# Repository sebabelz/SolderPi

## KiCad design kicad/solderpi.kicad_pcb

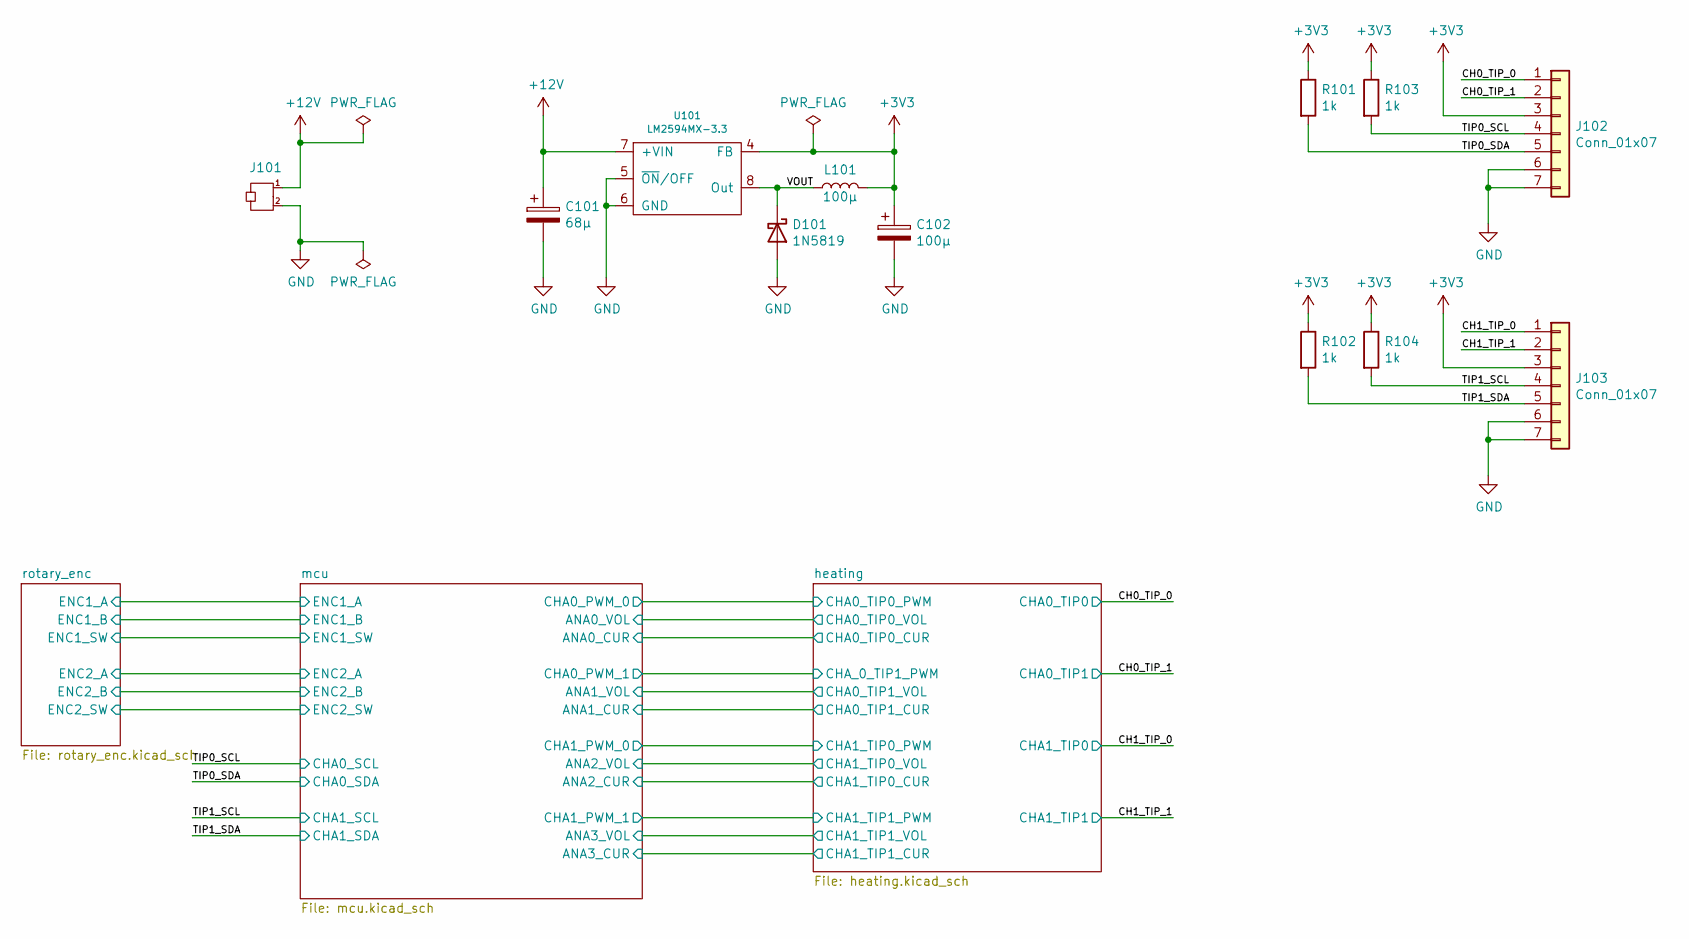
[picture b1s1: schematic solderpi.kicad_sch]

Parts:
C101: 68µ; CP_EIA-7343-30_AVX-N; Digikey 478-11114-1-ND
C102: 100µ; CP_EIA-7343-30_AVX-N; Digikey 478-9140-1-ND
D101: 1N5819; D_SOD-123; Digikey 1N5819HW-FDICT-ND
J101: CON_ULTRAFIT; ULTRAFIT_2_90; Digikey WM11586-ND
J102, J103: Conn_01x07; NANOFIT_7_90; Digikey WM16898-ND
L101: 100µ; L_Bourns_SRR0735A; Digikey SRR0735A-101MCT-ND
R101, R102, R103, R104: 1k; R_0603_1608Metric; Digikey RMCF0603FT1K00CT-ND
U101: LM2594MX-3.3; SOIC-8-1EP_3.9x4.9mm_P1.27mm_EP2.95x4.9mm_Mask2.71x3.4mm; Digikey LM2594MX-3.3/NOPBCT-ND

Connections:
+3V3: C102.1, J102.3, J103.3, L101.2, R101.1, R102.1, R103.1, R104.1, U101.4 (FB); also elsewhere on the board
+12V: C101.1, J101.1, U101.7 (+VIN); also elsewhere on the board
/CH0_TIP_0: J102.1; also elsewhere on the board
/CH0_TIP_1: J102.2; also elsewhere on the board
/CH1_TIP_0: J103.1; also elsewhere on the board
/CH1_TIP_1: J103.2; also elsewhere on the board
/TIP0_SCL: J102.4, R103.2; also elsewhere on the board
/TIP0_SDA: J102.5, R101.2; also elsewhere on the board
/TIP1_SCL: J103.4, R104.2; also elsewhere on the board
/TIP1_SDA: J103.5, R102.2; also elsewhere on the board
/VOUT: D101.1 (K), L101.1, U101.8 (Out)
GND: C101.2, C102.2, D101.2 (A), J101.2, J102.6, J102.7, J103.6, J103.7, U101.5 (~ON/OFF), U101.6 (GND); also elsewhere on the board

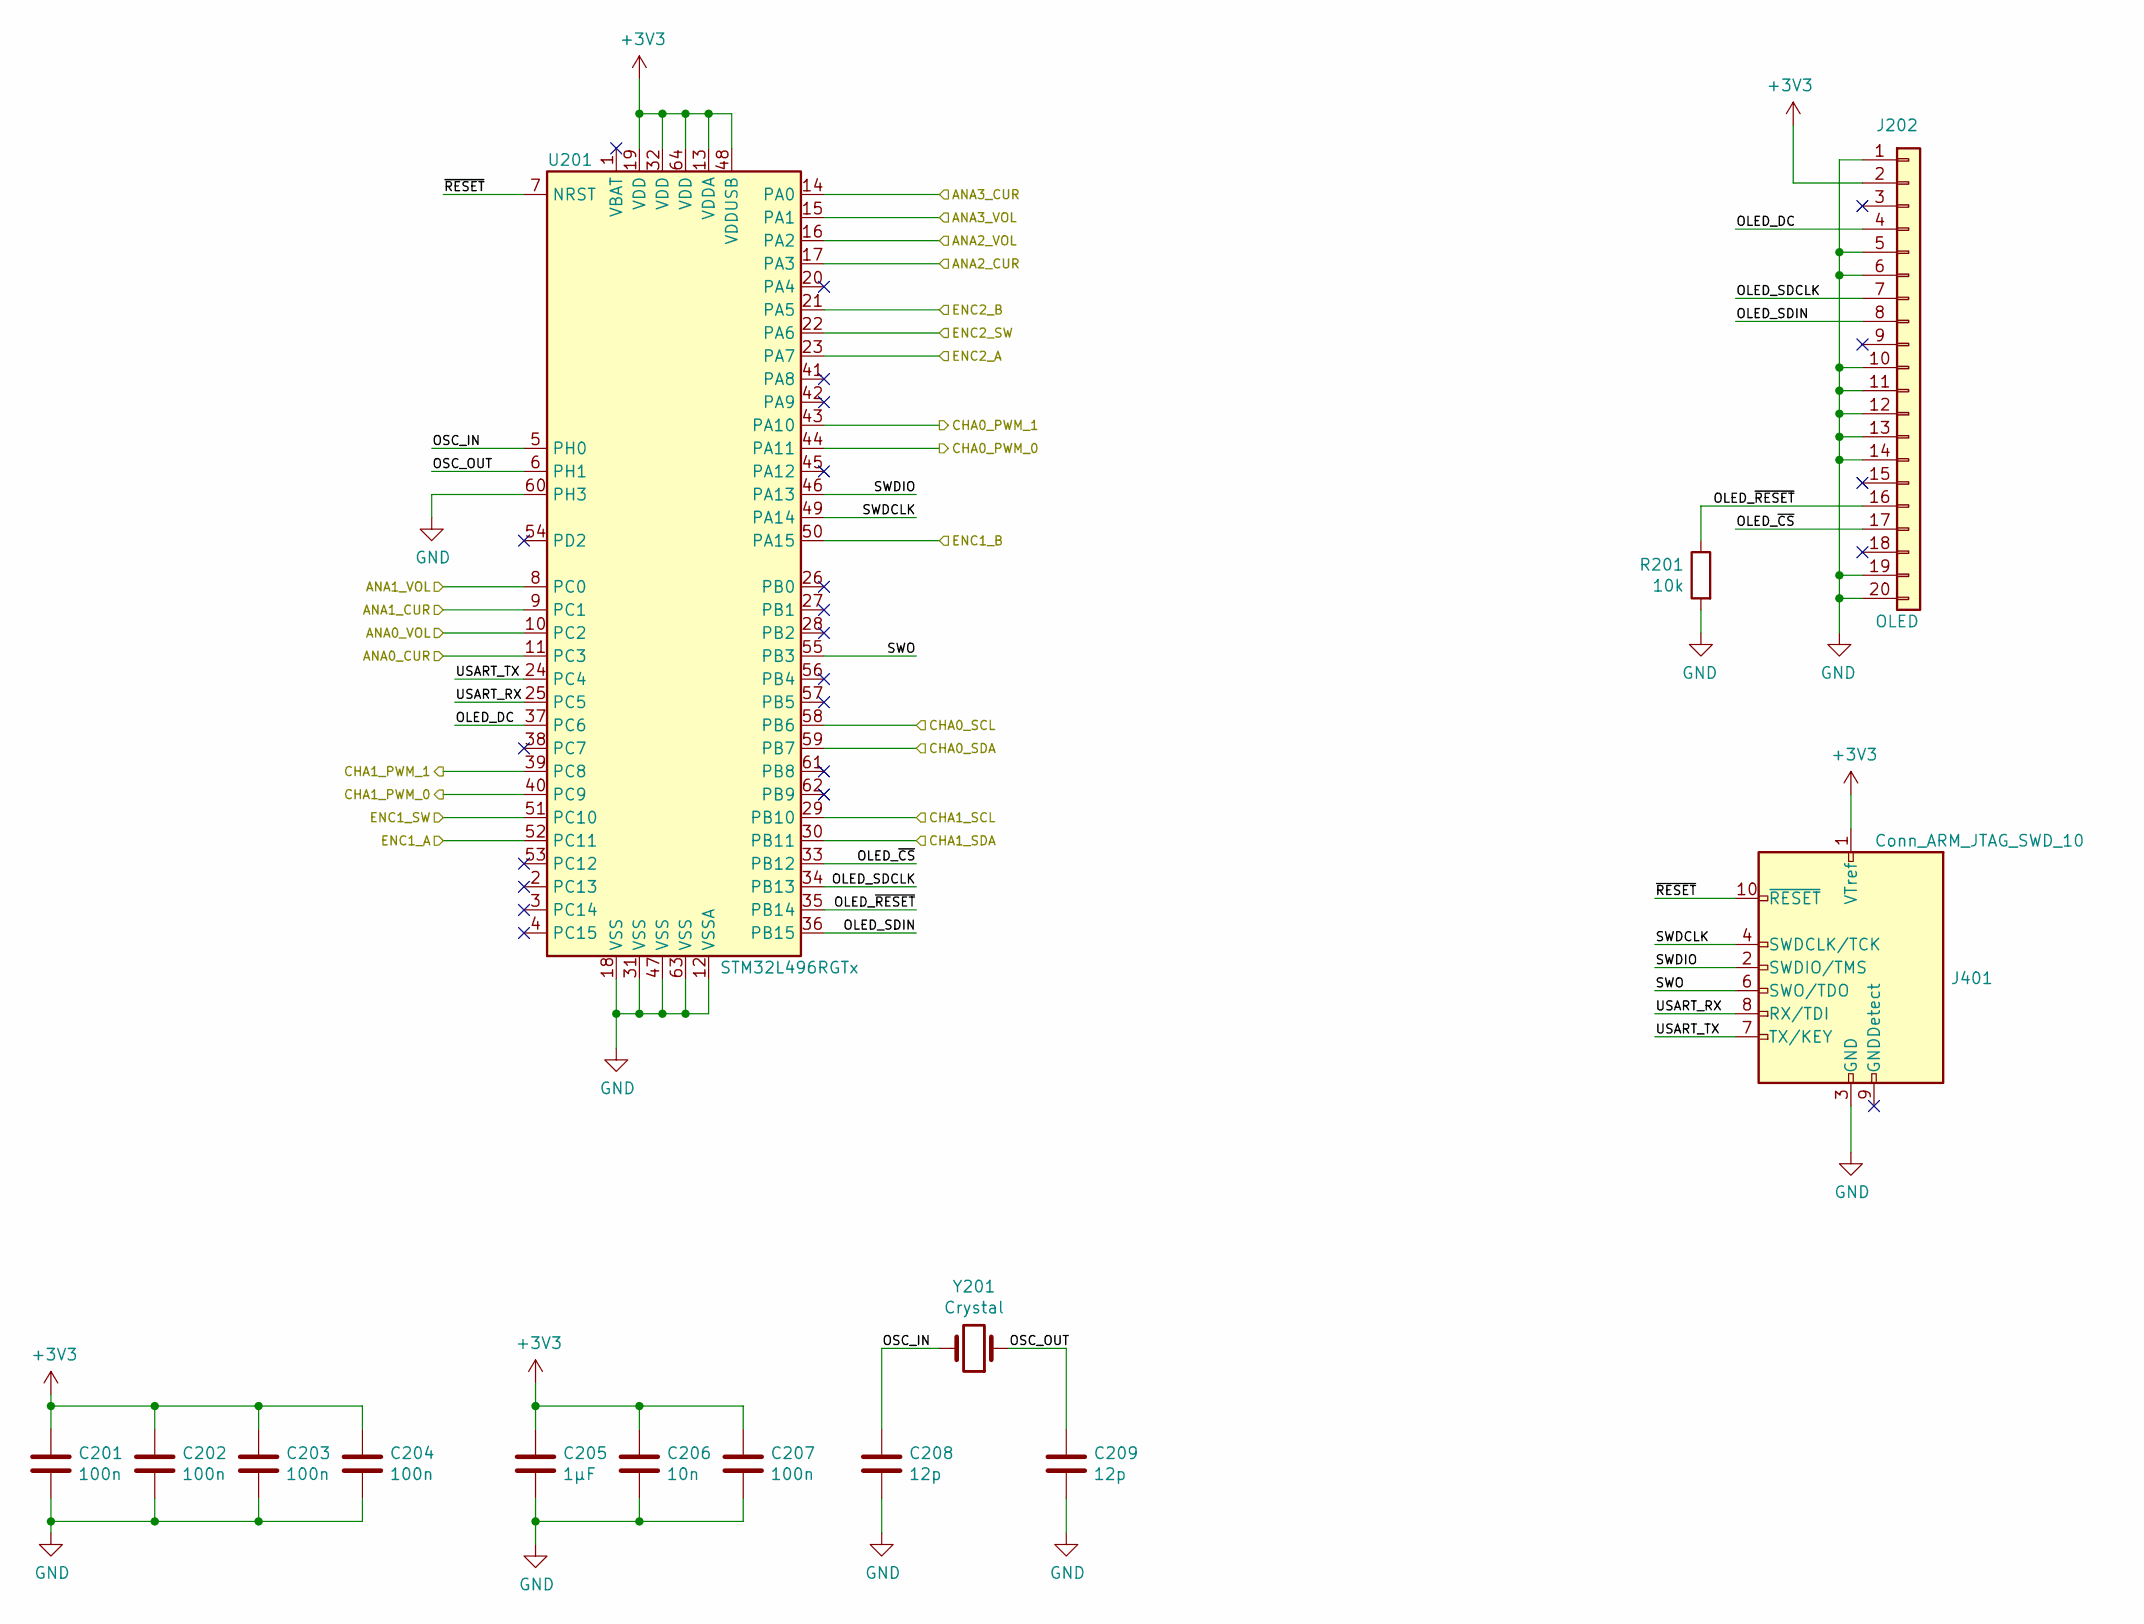
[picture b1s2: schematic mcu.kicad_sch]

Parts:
C201, C202, C203, C204, C207: 100n; R_0402_1005Metric; Digikey 1276-1001-1-ND
C205: 1µF; R_0402_1005Metric; Digikey 1276-1067-1-ND
C206: 10n; R_0402_1005Metric; Digikey 311-1042-1-ND
C208, C209: 12p; C_0603_1608Metric; Digikey 478-11444-1-ND
J202: OLED; NewHaven_OLED_256x64; Digikey SAM1093-20-ND
J401: Conn_ARM_JTAG_SWD_10; Tag-Connect_TC2050-IDC-FP_2x05_P1.27mm_Vertical
R201: 10k; R_0603_1608Metric; Digikey RMCF0603FT10K0CT-ND
U201: STM32L496RGTx; LQFP-64_10x10mm_P0.5mm; Digikey 497-17173-ND
Y201: Crystal; Crystal_SMD_Murata_XRCHA-2Pin_2,5x2mm; Digikey 490-9652-1-ND

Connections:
+3V3: C201.1, C202.1, C203.1, C204.1, C205.1, C206.1, C207.1, J202.2, J401.1 (VTref), U201.13 (VDDA), U201.19 (VDD), U201.32 (VDD), U201.48 (VDDUSB), U201.64 (VDD); also elsewhere on the board
/TIP0_SCL: U201.58 (PB6); also elsewhere on the board
/TIP0_SDA: U201.59 (PB7); also elsewhere on the board
/TIP1_SCL: U201.29 (PB10); also elsewhere on the board
/TIP1_SDA: U201.30 (PB11); also elsewhere on the board
/mcu/ANA0_CUR: U201.11 (PC3); also elsewhere on the board
/mcu/ANA0_VOL: U201.10 (PC2); also elsewhere on the board
/mcu/ANA1_CUR: U201.9 (PC1); also elsewhere on the board
/mcu/ANA1_VOL: U201.8 (PC0); also elsewhere on the board
/mcu/ANA2_CUR: U201.17 (PA3); also elsewhere on the board
/mcu/ANA2_VOL: U201.16 (PA2); also elsewhere on the board
/mcu/ANA3_CUR: U201.14 (PA0); also elsewhere on the board
/mcu/ANA3_VOL: U201.15 (PA1); also elsewhere on the board
/mcu/CHA0_PWM_0: U201.44 (PA11); also elsewhere on the board
/mcu/CHA0_PWM_1: U201.43 (PA10); also elsewhere on the board
/mcu/CHA1_PWM_0: U201.40 (PC9); also elsewhere on the board
/mcu/CHA1_PWM_1: U201.39 (PC8); also elsewhere on the board
/mcu/ENC1_A: U201.52 (PC11); also elsewhere on the board
/mcu/ENC1_B: U201.50 (PA15); also elsewhere on the board
/mcu/ENC1_SW: U201.51 (PC10); also elsewhere on the board
/mcu/ENC2_A: U201.23 (PA7); also elsewhere on the board
/mcu/ENC2_B: U201.21 (PA5); also elsewhere on the board
/mcu/ENC2_SW: U201.22 (PA6); also elsewhere on the board
/mcu/OLED_DC: J202.4, U201.37 (PC6)
/mcu/OLED_SDCLK: J202.7, U201.34 (PB13)
/mcu/OLED_SDIN: J202.8, U201.36 (PB15)
/mcu/OLED_~CS: J202.17, U201.33 (PB12)
/mcu/OLED_~RESET: J202.16, R201.1, U201.35 (PB14)
/mcu/OSC_IN: C208.1, U201.5 (PH0), Y201.2
/mcu/OSC_OUT: C209.1, U201.6 (PH1), Y201.1
/mcu/SWDCLK: J401.4 (SWDCLK/TCK), U201.49 (PA14)
/mcu/SWDIO: J401.2 (SWDIO/TMS), U201.46 (PA13)
/mcu/SWO: J401.6 (SWO/TDO), U201.55 (PB3)
/mcu/USART_RX: J401.8 (RX/TDI), U201.25 (PC5)
/mcu/USART_TX: J401.7 (TX/KEY), U201.24 (PC4)
/mcu/~RESET: J401.10 (~RESET), U201.7 (NRST)
GND: C201.2, C202.2, C203.2, C204.2, C205.2, C206.2, C207.2, C208.2, C209.2, J202.1, J202.5, J202.6, J202.10, J202.11, J202.12, J202.13, J202.14, J202.19, J202.20, J401.3 (GND), J401.5 (GND), R201.2, U201.12 (VSSA), U201.18 (VSS), U201.31 (VSS), U201.47 (VSS), U201.60 (PH3), U201.63 (VSS); also elsewhere on the board

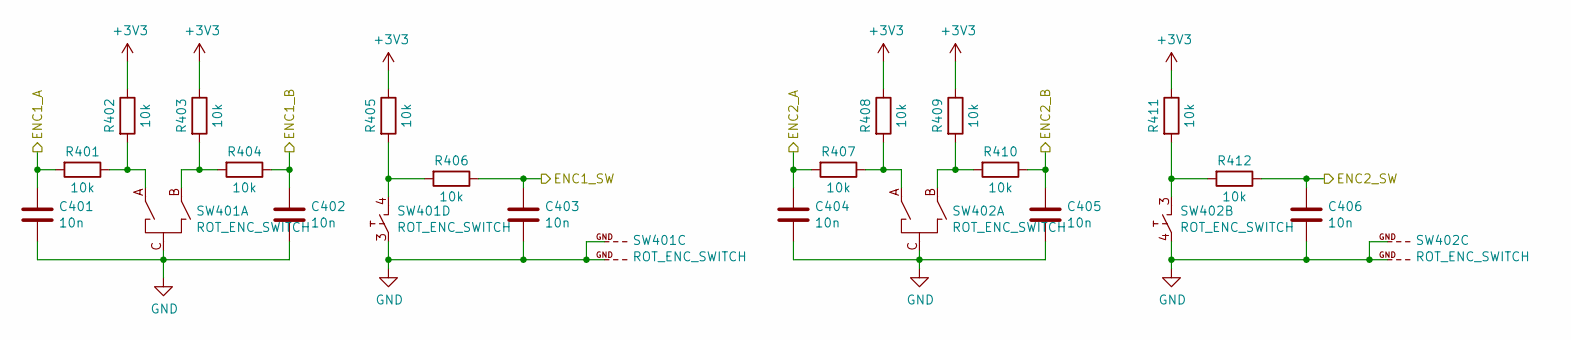
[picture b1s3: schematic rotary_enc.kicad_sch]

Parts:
C401, C402, C403, C404, C405, C406: 10n; C_0805_2012Metric; Digikey 732-8061-1-ND
R401, R402, R403, R404, R405, R406, R407, R408, R409, R410, R411, R412: 10k; R_0805_2012Metric; Digikey 311-10.0KCRCT-ND
SW401, SW402: ROT_ENC_SWITCH; EC12E

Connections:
+3V3: R402.1, R403.1, R405.1, R408.1, R409.1, R411.1; also elsewhere on the board
/mcu/ENC1_A: C401.1, R401.2; also elsewhere on the board
/mcu/ENC1_B: C402.1, R404.1; also elsewhere on the board
/mcu/ENC1_SW: C403.1, R406.1; also elsewhere on the board
/mcu/ENC2_A: C404.1, R407.2; also elsewhere on the board
/mcu/ENC2_B: C405.1, R410.1; also elsewhere on the board
/mcu/ENC2_SW: C406.1, R412.1; also elsewhere on the board
GND: C401.2, C402.2, C403.2, C404.2, C405.2, C406.2, SW401.3, SW401.C, SW401.GND, SW402.4, SW402.C, SW402.GND; also elsewhere on the board
unnamed: R401.1, R402.2, SW401.A
unnamed: R403.2, R404.2, SW401.B
unnamed: R405.2, R406.2, SW401.4
unnamed: R407.1, R408.2, SW402.A
unnamed: R409.2, R410.2, SW402.B
unnamed: R411.2, R412.2, SW402.3

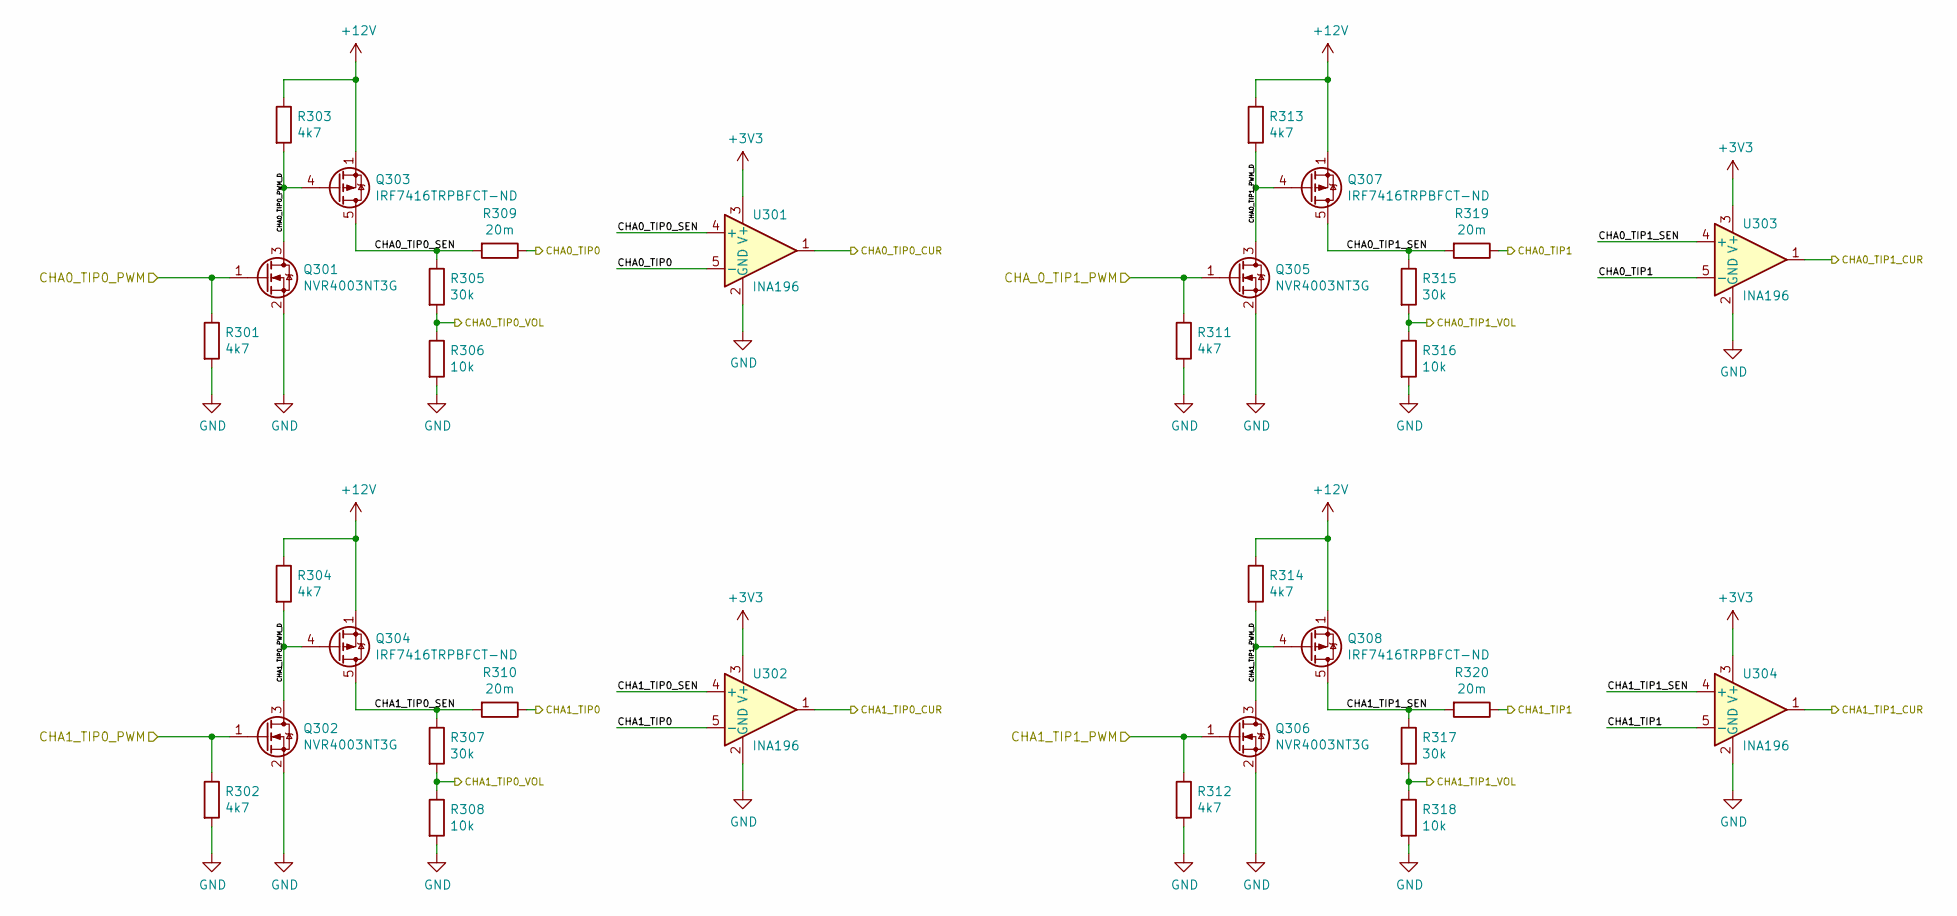
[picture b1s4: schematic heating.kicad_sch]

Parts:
Q301, Q302, Q305, Q306: NVR4003NT3G; SOT-23; Digikey NVR4003NT3GOSCT-ND
Q303, Q304, Q307, Q308: IRF7416TRPBFCT-ND; SO-8_3.9x4.9mm_P1.27mm; Digikey IRF7416TRPBFCT-ND
R301, R302, R303, R304, R311, R312, R313, R314: 4k7; R_0805_2012Metric; Digikey CR0805-FX-4701GLFTR-ND
R305, R307, R315, R317: 30k; R_0603_1608Metric; Digikey RMCF0603FT30K0CT-ND
R306, R308, R316, R318: 10k; R_0603_1608Metric; Digikey RMCF0603FT10K0CT-ND
R309, R310, R319, R320: 20m; R_2010_5025Metric; Digikey 541-10266-1-ND
U301, U302, U303, U304: INA196; SOT-23-5; Digikey 296-17166-1-ND

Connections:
+3V3: U301.3 (V+), U302.3 (V+), U303.3 (V+), U304.3 (V+); also elsewhere on the board
+12V: Q303.1 (S), Q303.2 (S), Q303.3 (S), Q304.1 (S), Q304.2 (S), Q304.3 (S), Q307.1 (S), Q307.2 (S), Q307.3 (S), Q308.1 (S), Q308.2 (S), Q308.3 (S), R303.1, R304.1, R313.1, R314.1; also elsewhere on the board
/CH0_TIP_0: R309.1, U301.5 (-); also elsewhere on the board
/CH0_TIP_1: R319.1, U303.5 (-); also elsewhere on the board
/CH1_TIP_0: R310.1, U302.5 (-); also elsewhere on the board
/CH1_TIP_1: R320.1, U304.5 (-); also elsewhere on the board
/heating/CHA0_TIP0_PWM_D: Q301.3 (D), Q303.4 (G), R303.2
/heating/CHA0_TIP0_SEN: Q303.5 (D), Q303.6 (D), Q303.7 (D), Q303.8 (D), R305.1, R309.2, U301.4 (+)
/heating/CHA0_TIP1_PWM_D: Q305.3 (D), Q307.4 (G), R313.2
/heating/CHA0_TIP1_SEN: Q307.5 (D), Q307.6 (D), Q307.7 (D), Q307.8 (D), R315.1, R319.2, U303.4 (+)
/heating/CHA1_TIP0_PWM_D: Q302.3 (D), Q304.4 (G), R304.2
/heating/CHA1_TIP0_SEN: Q304.5 (D), Q304.6 (D), Q304.7 (D), Q304.8 (D), R307.1, R310.2, U302.4 (+)
/heating/CHA1_TIP1_PWM_D: Q306.3 (D), Q308.4 (G), R314.2
/heating/CHA1_TIP1_SEN: Q308.5 (D), Q308.6 (D), Q308.7 (D), Q308.8 (D), R317.1, R320.2, U304.4 (+)
/mcu/ANA0_CUR: U301.1; also elsewhere on the board
/mcu/ANA0_VOL: R305.2, R306.1; also elsewhere on the board
/mcu/ANA1_CUR: U303.1; also elsewhere on the board
/mcu/ANA1_VOL: R315.2, R316.1; also elsewhere on the board
/mcu/ANA2_CUR: U302.1; also elsewhere on the board
/mcu/ANA2_VOL: R307.2, R308.1; also elsewhere on the board
/mcu/ANA3_CUR: U304.1; also elsewhere on the board
/mcu/ANA3_VOL: R317.2, R318.1; also elsewhere on the board
/mcu/CHA0_PWM_0: Q301.1 (G), R301.1; also elsewhere on the board
/mcu/CHA0_PWM_1: Q305.1 (G), R311.1; also elsewhere on the board
/mcu/CHA1_PWM_0: Q302.1 (G), R302.1; also elsewhere on the board
/mcu/CHA1_PWM_1: Q306.1 (G), R312.1; also elsewhere on the board
GND: Q301.2 (S), Q302.2 (S), Q305.2 (S), Q306.2 (S), R301.2, R302.2, R306.2, R308.2, R311.2, R312.2, R316.2, R318.2, U301.2 (GND), U302.2 (GND), U303.2 (GND), U304.2 (GND); also elsewhere on the board

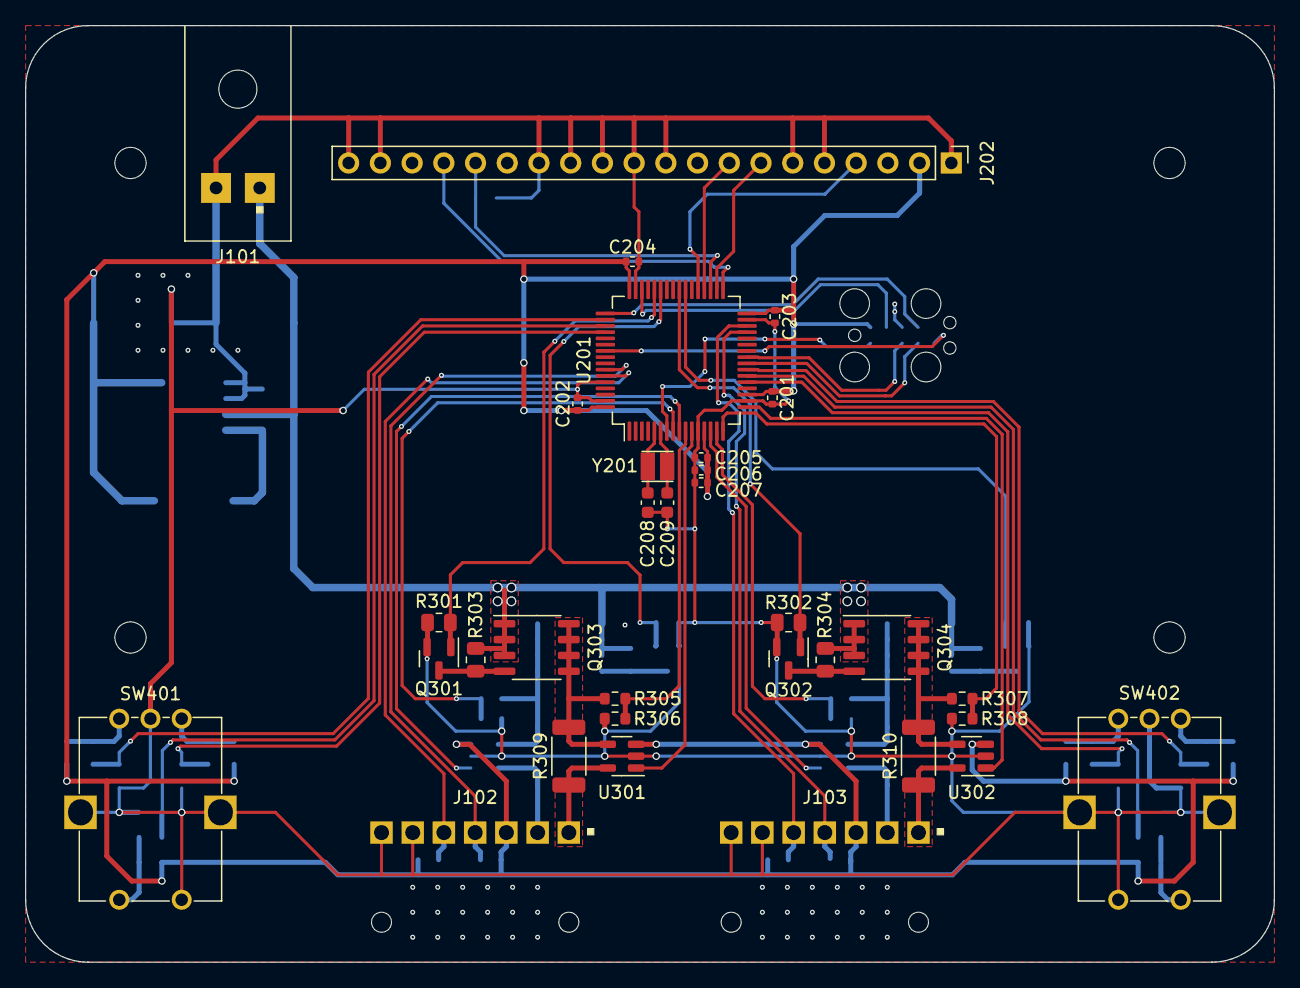
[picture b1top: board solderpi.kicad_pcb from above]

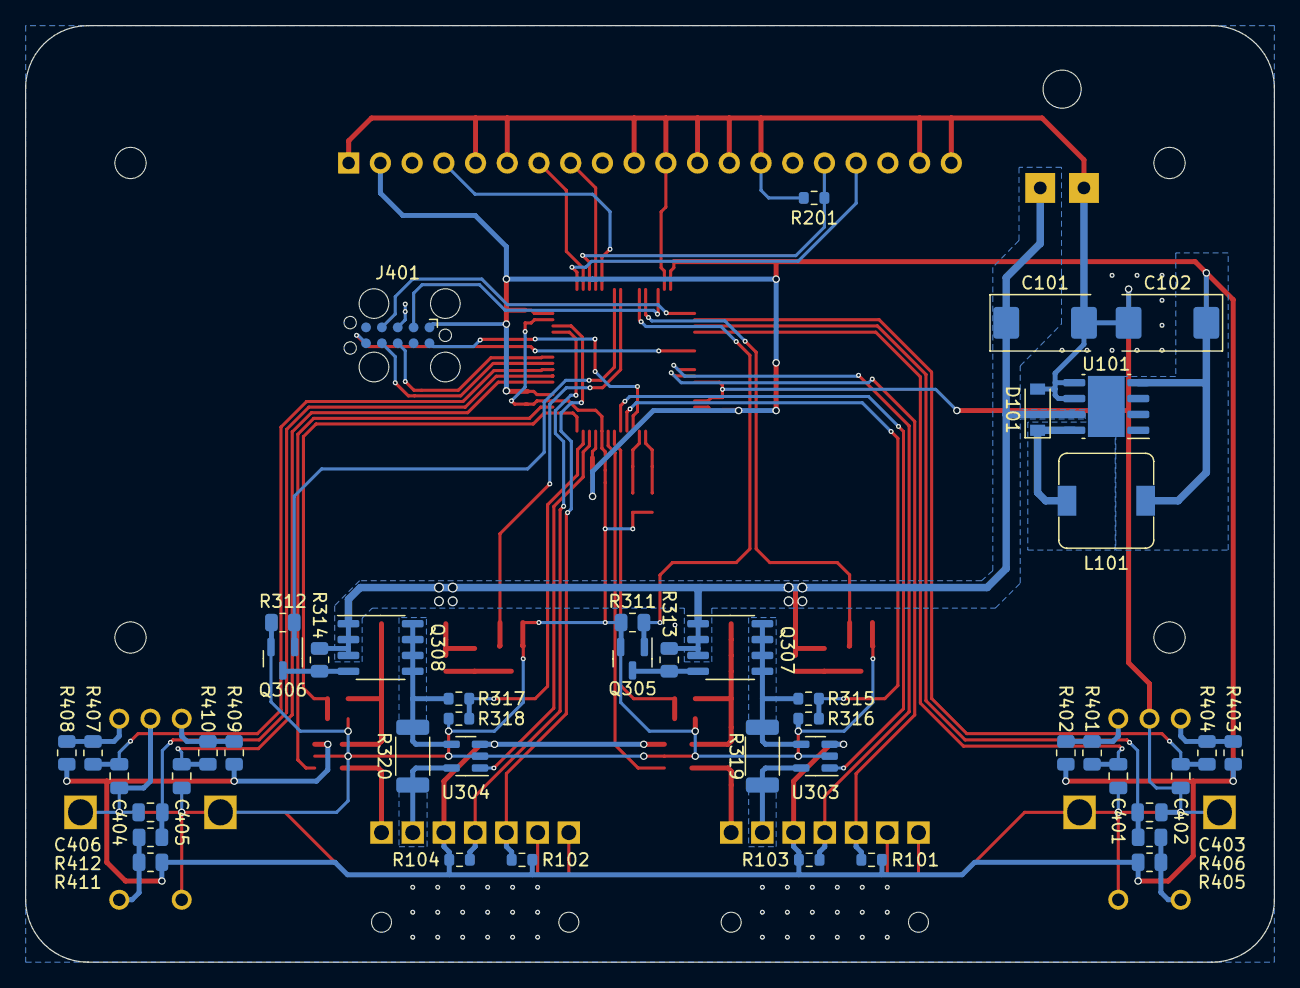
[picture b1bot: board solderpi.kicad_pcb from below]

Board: 2 copper layers, 100.0 x 75.0 mm, 78 parts (45 on the bottom side), 57 nets.

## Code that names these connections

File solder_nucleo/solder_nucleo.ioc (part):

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Mcu.Name=STM32F446R(C-E)Tx
Mcu.Package=LQFP64
Mcu.UserName=STM32F446RETx
PA0-WKUP.GPIOParameters=GPIO_Speed
PA0-WKUP.GPIO_Speed=GPIO_SPEED_FREQ_HIGH
PA0-WKUP.Signal=S_TIM5_CH1
PA1.GPIOParameters=GPIO_Speed
PA1.GPIO_Speed=GPIO_SPEED_FREQ_HIGH
PA1.Signal=S_TIM5_CH2
PA10.GPIOParameters=GPIO_Label,GPIO_ModeDefaultEXTI
PA10.GPIO_Label=ENC_CH_A
PA10.GPIO_ModeDefaultEXTI=GPIO_MODE_IT_FALLING
PA10.Signal=GPXTI10
PA13.GPIOParameters=GPIO_Label
PA13.GPIO_Label=TMS
PA13.Mode=Serial_Wire
PA13.Signal=SYS_JTMS-SWDIO
PA14.GPIOParameters=GPIO_Label
PA14.GPIO_Label=TCK
PA14.Mode=Serial_Wire
PA14.Signal=SYS_JTCK-SWCLK
PA2.GPIOParameters=GPIO_Label
PA2.GPIO_Label=USART_TX
PA2.Mode=Asynchronous
PA2.Signal=USART2_TX
PA3.GPIOParameters=GPIO_Label
PA3.GPIO_Label=USART_RX
PA3.Mode=Asynchronous
PA3.Signal=USART2_RX
PA4.GPIOParameters=GPIO_Label
PA4.GPIO_Label=CMP
PA4.Signal=GPIO_Output
PA5.GPIOParameters=GPIO_Label
PA5.GPIO_Label=LD2 [Green Led]
PA5.Signal=GPIO_Output
PA6.Signal=S_TIM3_CH1
PA7.Signal=S_TIM3_CH2
PB3.GPIOParameters=GPIO_Label
PB3.GPIO_Label=SWO
PB3.Signal=SYS_JTDO-SWO
PB4.GPIOParameters=GPIO_Label
PB4.GPIO_Label=ENC_CH_B
PB4.Signal=GPIO_Input
PB5.GPIOParameters=GPIO_Label
PB5.GPIO_Label=BTN
PB5.Signal=GPXTI5
PB8.GPIOParameters=GPIO_PuPdOD
PB8.GPIO_PuPdOD=GPIO_PULLUP
PB8.Mode=I2C
PB8.Signal=I2C1_SCL
PB9.GPIOParameters=GPIO_PuPdOD
PB9.GPIO_PuPdOD=GPIO_PULLUP
PB9.Mode=I2C
PB9.Signal=I2C1_SDA
PC13.GPIOParameters=GPIO_Label,GPIO_ModeDefaultEXTI
PC13.GPIO_Label=B1 [Blue PushButton]
PC13.GPIO_ModeDefaultEXTI=GPIO_MODE_IT_FALLING
PC13.Signal=GPXTI13
PC14-OSC32_IN.Mode=LSE-External-Oscillator
PC14-OSC32_IN.Signal=RCC_OSC32_IN
PC15-OSC32_OUT.Mode=LSE-External-Oscillator
PC15-OSC32_OUT.Signal=RCC_OSC32_OUT
PC6.GPIOParameters=GPIO_PuPdOD
PC6.GPIO_PuPdOD=GPIO_NOPULL
PC6.Mode=I2C
PC6.Signal=FMPI2C1_SCL
PC7.GPIOParameters=GPIO_PuPdOD
PC7.GPIO_PuPdOD=GPIO_NOPULL
PC7.Mode=I2C
PC7.Signal=FMPI2C1_SDA
PH0-OSC_IN.Mode=HSE-External-Oscillator
PH0-OSC_IN.Signal=RCC_OSC_IN
PH1-OSC_OUT.Mode=HSE-External-Oscillator
PH1-OSC_OUT.Signal=RCC_OSC_OUT
RCC.HSE_VALUE=8000000
RCC.SYSCLKFreq_VALUE=84000000
RCC.SYSCLKSource=RCC_SYSCLKSOURCE_PLLCLK
board=NUCLEO-F446RE
boardIOC=true

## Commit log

2018-05-06 pcbs added
2018-05-06 bom added
2018-05-06 changed bom
2018-05-08 reworked current path on boards and added new gerber files
2018-05-15 added simple encoder
2018-05-25 updated simple controller, simple encoder
2018-05-26 updated simple controller, simple encoder (3D Packages)
2018-05-28 fixed vcc,vdd on opAmp
2018-05-31 fixing op amp (iron,tweezer)
2018-09-27 console View added
2018-09-27 reworked Terminal connection
2018-09-28 settings updated automatically
2018-11-18 updated Schematic from lib
2019-01-26 iron drills deleted
2019-03-07 qt ui added
2019-03-11 parts reworked
2019-03-26 changed part number ad7995
2019-03-27 read adc after pwm on state
2019-03-29 added button interrupt
2019-03-29 wip on capture software
2019-03-31 WIP: remove blocking TC function
2019-03-31 recording stops after heating up
2019-04-03 working
2019-04-14 arduino pid added
2019-04-18 pid settings changed
2019-07-27 basic configuration of nucleo board
2019-07-28 SSD1306 support added
2019-08-08 changed project to cpp
2019-08-08 working UART-Debugging connection
2019-08-08 debugging fmi2c
2019-08-09 reworked AD7995
2019-08-11 reworked PID
2019-08-11 working control parameters
2019-08-15 updated iron
2019-08-15 changed encoder to interrupt mode
2019-08-15 reworked iron parts
2019-08-18 reworked SolderingIron class
2019-08-21 i2c_buffer pcb added
2019-08-21 initial Commit controller Board
2019-08-23 wip connect mcu
2019-08-23 solderingIron class refactored
2019-08-23 circuit fully connected
2019-08-26 shottky diode added to iron/tweezer
2019-08-28 iron tweezer updated
2019-09-17 boms reworked
2021-08-15 kicad version pcb
2021-08-16 refactored debug connector
